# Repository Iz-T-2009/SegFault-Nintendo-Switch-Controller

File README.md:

# SegFault (Nintendo Switch Controller)
### DownTilt -> jab x3 -> PowerDunk

<b> uwa!! so temperate ♫ </b>

# --*update section*--
### scroll down for changelog and POC(s)!

### (current) current version!!!... >:3
this version was.. interesting to say the least. lots of issues were arising due to the choice of strictly not using matrix wiring to ensure the design doesn't look complex, andddd it always ends up more complex. more buttons were added! although.. that trade off may not be worth it.

<b>design!</b>

<b>3d render!</b>

anyways.. this is v0.1 :D

i decided to go with a simple design of purely cherry mx switches and a raspberry pi pico W for it's processing speed and polling rate. certain ground pins are daisy chained, as we're not dealing with much voltage here whatsoever. the traces are currently set to 9.84 mils, this is safe for the amount of current we're dealing with, which is about 150mA (max) with wifi capabilities in action. as for firmware, the GP2040CE firmware is going to be used until the custom firmware is done; and that might be a while.

### (used to be) current version!! :3
so.. it's been a bit since v0.1. we're currently on v0.2. i've added a display, changed out the layout a bit, and stuff is looking just a bit better. it always has me thinking "ohh my god this looks amazing!" with the display now. i'm sure it'll be nice when it's fully done.

### and a 3d render!!!... >:3
 -->

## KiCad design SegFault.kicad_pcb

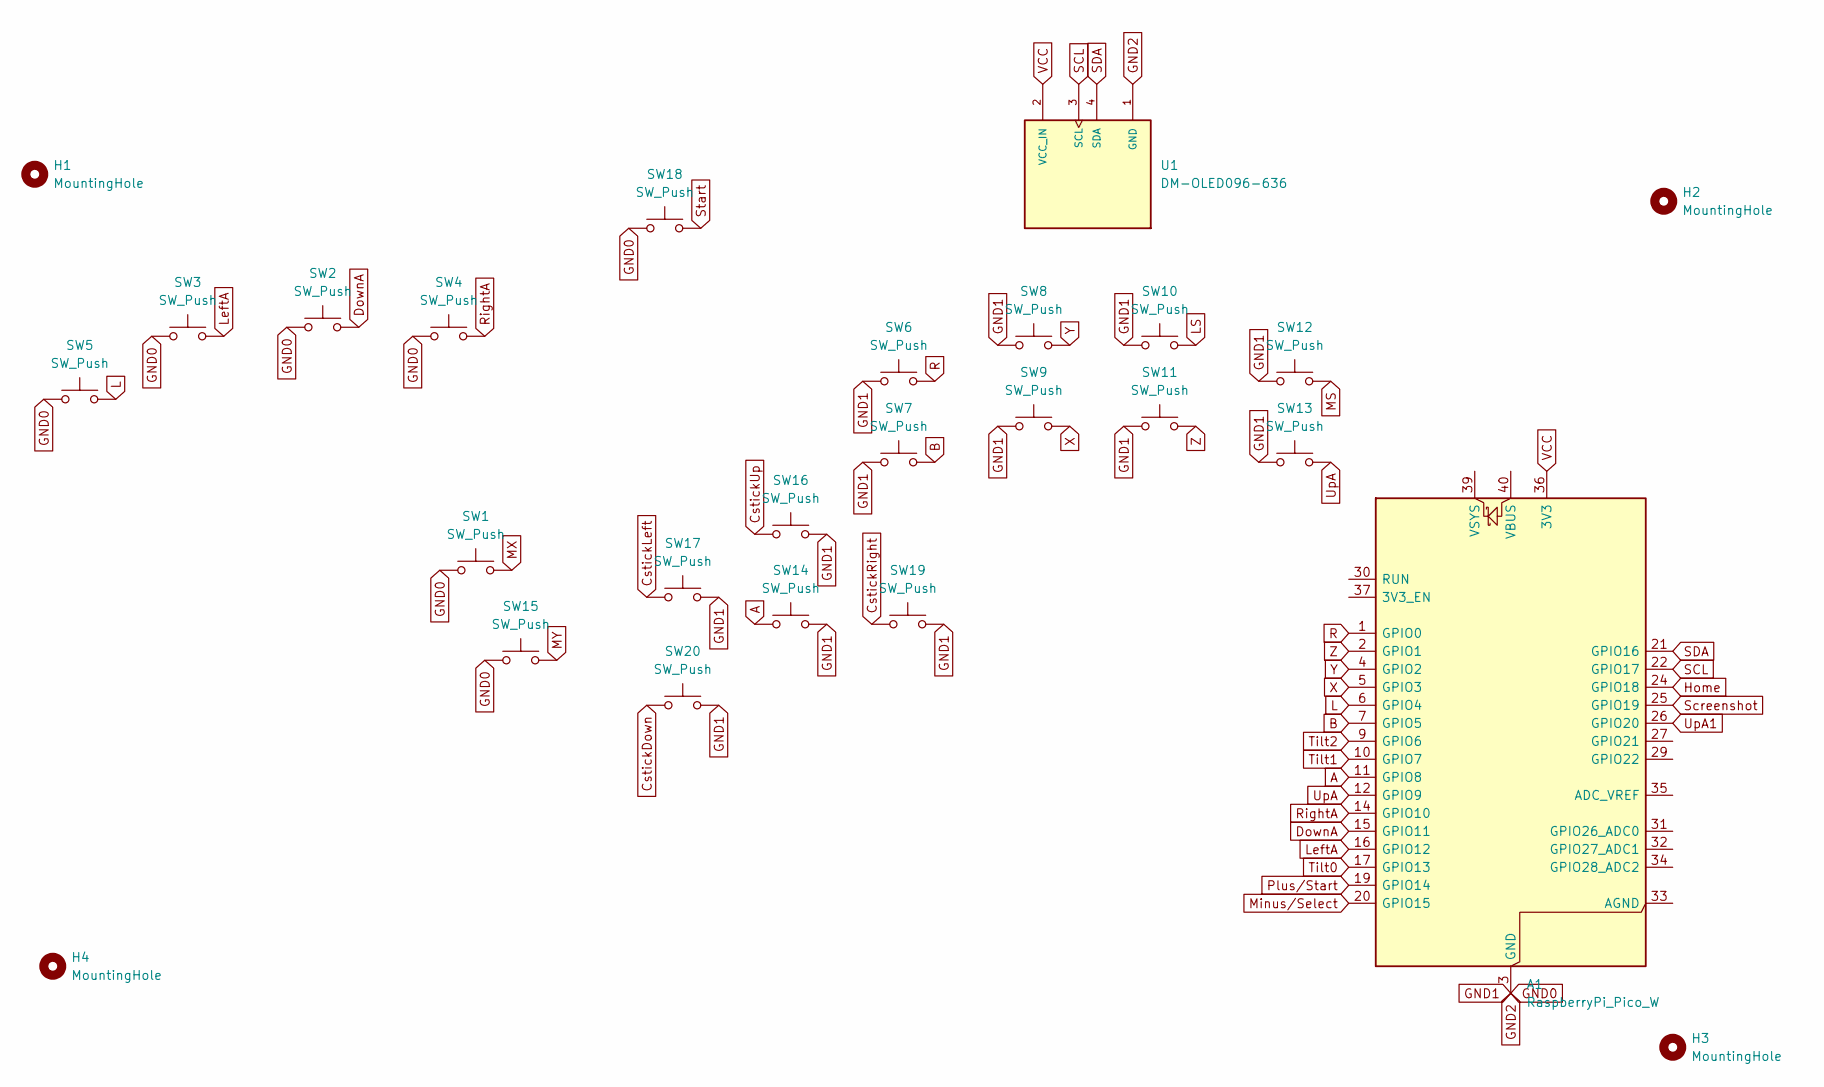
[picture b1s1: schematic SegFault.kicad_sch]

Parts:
A1: RaspberryPi_Pico_W; RaspberryPi_Pico_W_SMD_HandSolder
H1, H2, H3, H4: MountingHole; MountingHole_2.2mm_M2
SW1, SW2, SW3, SW4, SW5, SW6, SW7, SW8, SW9, SW10, SW11, SW12, SW13, SW14, SW15, SW16, SW17, SW18, SW19, SW20: SW_Push; SW_Cherry_MX_1.00u_PCB
U1: DM-OLED096-636; MODULE_DM-OLED096-636; PARTREV 2018-09-10

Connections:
A: A1.11 (GPIO8), SW14.1
B: A1.7 (GPIO5), SW7.2
CstickDown: SW20.1
CstickLeft: SW17.1
CstickRight: SW19.1
CstickUp: SW16.1
DownA: A1.15 (GPIO11), SW2.2
GND0: A1.3 (GND), A1.8 (GND), A1.13 (GND), A1.18 (GND), A1.23 (GND), A1.28 (GND), A1.38 (GND), SW1.1, SW2.1, SW3.1, SW4.1, SW5.1, SW6.1, SW7.1, SW8.1, SW9.1, SW10.1, SW11.1, SW12.1, SW13.1, SW14.2, SW15.1, SW16.2, SW17.2, SW18.1, SW19.2, SW20.2, U1.1 (GND)
Home: A1.24 (GPIO18)
L: A1.6 (GPIO4), SW5.2
LS: SW10.2
LeftA: A1.16 (GPIO12), SW3.2
MS: SW12.2
MX: SW1.2
MY: SW15.2
Minus/Select: A1.20 (GPIO15)
Plus/Start: A1.19 (GPIO14)
R: A1.1 (GPIO0), SW6.2
RightA: A1.14 (GPIO10), SW4.2
SCL: A1.22 (GPIO17), U1.3 (SCL)
SDA: A1.21 (GPIO16), U1.4 (SDA)
Screenshot: A1.25 (GPIO19)
Start: SW18.2
Tilt0: A1.17 (GPIO13)
Tilt1: A1.10 (GPIO7)
Tilt2: A1.9 (GPIO6)
UpA: A1.12 (GPIO9), SW13.2
UpA1: A1.26 (GPIO20)
VCC: A1.36 (3V3), U1.2 (VCC_IN)
X: A1.5 (GPIO3), SW9.2
Y: A1.4 (GPIO2), SW8.2
Z: A1.2 (GPIO1), SW11.2

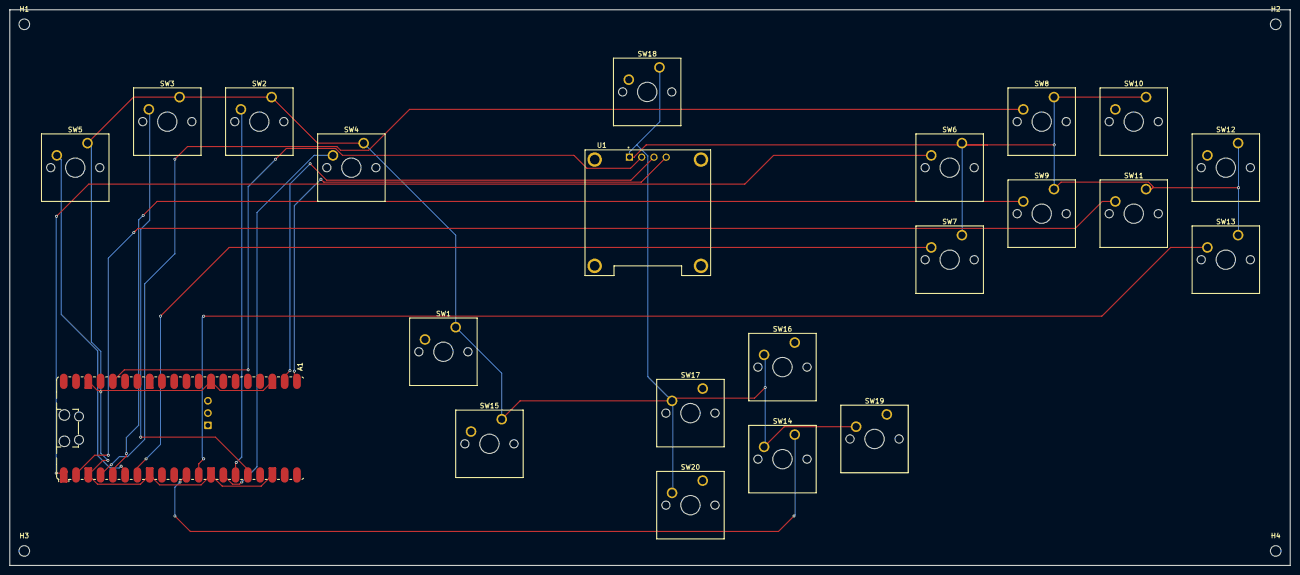
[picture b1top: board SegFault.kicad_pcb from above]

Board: 2 copper layers, 265.0 x 115.0 mm, 26 parts (0 on the bottom side), 15 nets.

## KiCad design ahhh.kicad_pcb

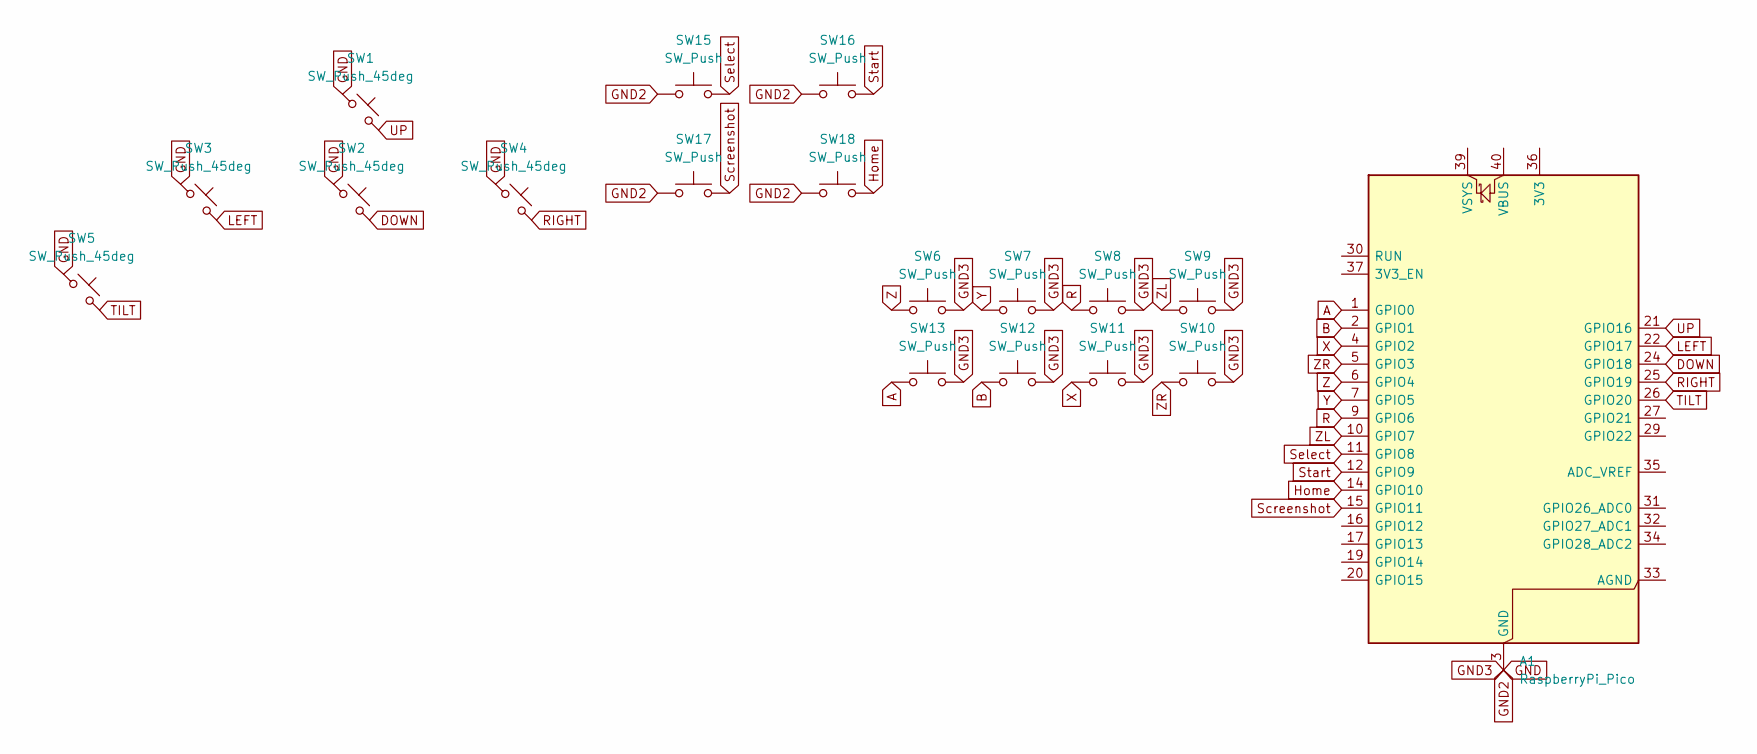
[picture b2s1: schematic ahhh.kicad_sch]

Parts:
A1: RaspberryPi_Pico; RaspberryPi_Pico_Common_Unspecified
SW1, SW2, SW3, SW4, SW5: SW_Push_45deg; SW_Cherry_MX_1.00u_PCB
SW6, SW7, SW8, SW9, SW10, SW11, SW12, SW13, SW15, SW16, SW17, SW18: SW_Push; SW_Cherry_MX_1.00u_PCB

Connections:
A: A1.1 (GPIO0), SW13.1
B: A1.2 (GPIO1), SW12.1
DOWN: A1.24 (GPIO18), SW2.2
GND: A1.3 (GND), A1.8 (GND), A1.13 (GND), A1.18 (GND), A1.23 (GND), A1.28 (GND), A1.38 (GND), SW1.1, SW2.1, SW3.1, SW4.1, SW5.1, SW6.2, SW7.2, SW8.2, SW9.2, SW10.2, SW11.2, SW12.2, SW13.2, SW15.1, SW16.1, SW17.1, SW18.1
Home: A1.14 (GPIO10), SW18.2
LEFT: A1.22 (GPIO17), SW3.2
R: A1.9 (GPIO6), SW8.1
RIGHT: A1.25 (GPIO19), SW4.2
Screenshot: A1.15 (GPIO11), SW17.2
Select: A1.11 (GPIO8), SW15.2
Start: A1.12 (GPIO9), SW16.2
TILT: A1.26 (GPIO20), SW5.2
UP: A1.21 (GPIO16), SW1.2
X: A1.4 (GPIO2), SW11.1
Y: A1.7 (GPIO5), SW7.1
Z: A1.6 (GPIO4), SW6.1
ZL: A1.10 (GPIO7), SW9.1
ZR: A1.5 (GPIO3), SW10.1

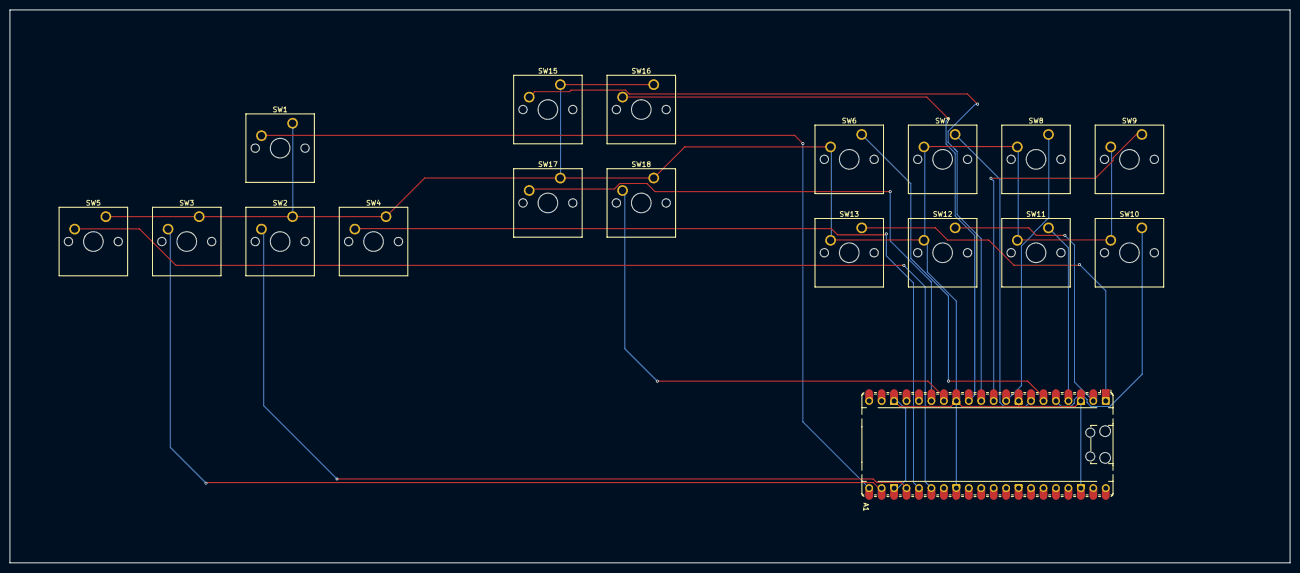
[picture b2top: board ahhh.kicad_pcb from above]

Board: 2 copper layers, 261.1 x 112.8 mm, 18 parts (0 on the bottom side), 18 nets.

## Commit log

2026-03-09 Rename Screenshot From 2026-03-09 19-40-37.png to PCB_DESIGN_SCR
2026-03-09 Rename PCB_DESIGN_SCR to PCB_DESIGN_SCR.png
2026-03-09 add screenshot to readme.md
2026-03-09 update readme
    change "jab 3x" to "jab x3" purely for cosmetic purposes
    note that it may be etched into the controller case at a later time, I just want the description to match the etched text
2026-04-01 v0.2
2026-04-01 update image presented for v0.2 to include edge cuts and traces
2026-04-09 new revision! officially v0.2
2026-04-09 Update LICENSE
2026-04-27 Reformat README.md
2026-04-27 Fix spelling mistake
